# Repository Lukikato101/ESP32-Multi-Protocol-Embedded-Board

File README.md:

# Multi-Protocol ESP32-Based Embedded Board

## Project Overview
This project is my personal embedded hardware design built around the ESP32 platform. I created this board as a compact and flexible prototype for wireless and connected applications. The design is made in KiCad and focuses on a clean PCB structure, practical connectivity, and room for future development.

I made this project to improve my understanding of embedded systems, PCB design, and hardware prototyping. It also helped me practice turning an idea into a more structured and realistic electronic board.

---

## What I Built
This board is centered around an ESP32-based module and several connector interfaces that allow me to connect external components or modules when needed. The layout is simple, organized, and intended to be useful for experimentation and further development.

### Main Parts of the Project
- ESP32-based controller module
- Connector headers for expansion and external connections
- PCB layout designed for practical routing and assembly
- A compact hardware platform for embedded projects

---

## Why I Made This Project
I wanted to build a small hardware platform that could be used as a base for future electronics projects. This board gives me a starting point for testing ideas, connecting modules, and exploring how embedded systems can be designed in a more complete way.

This project is especially useful for:
- learning embedded hardware design
- building wireless-based prototypes
- testing ideas before making a larger product
- improving my PCB and circuit layout skills

---

## Project Images

### PCB Layout

### Board View 1

### Board View 2

---

## What I Learned
Through this project, I improved my understanding of:
- embedded system architecture
- PCB schematic and layout design
- component placement and routing
- hardware organization for practical use
- building a project from concept to board design

---

## Future Development
I can continue developing this project by:
- adding power management features
- integrating sensors or actuators
- supporting more communication interfaces
- turning it into a more complete prototype
- testing it in real applications

---

## Conclusion
This project is an important part of my learning in electronics and embedded hardware. I built it as a personal prototype to strengthen my skills and create a solid foundation for future projects.

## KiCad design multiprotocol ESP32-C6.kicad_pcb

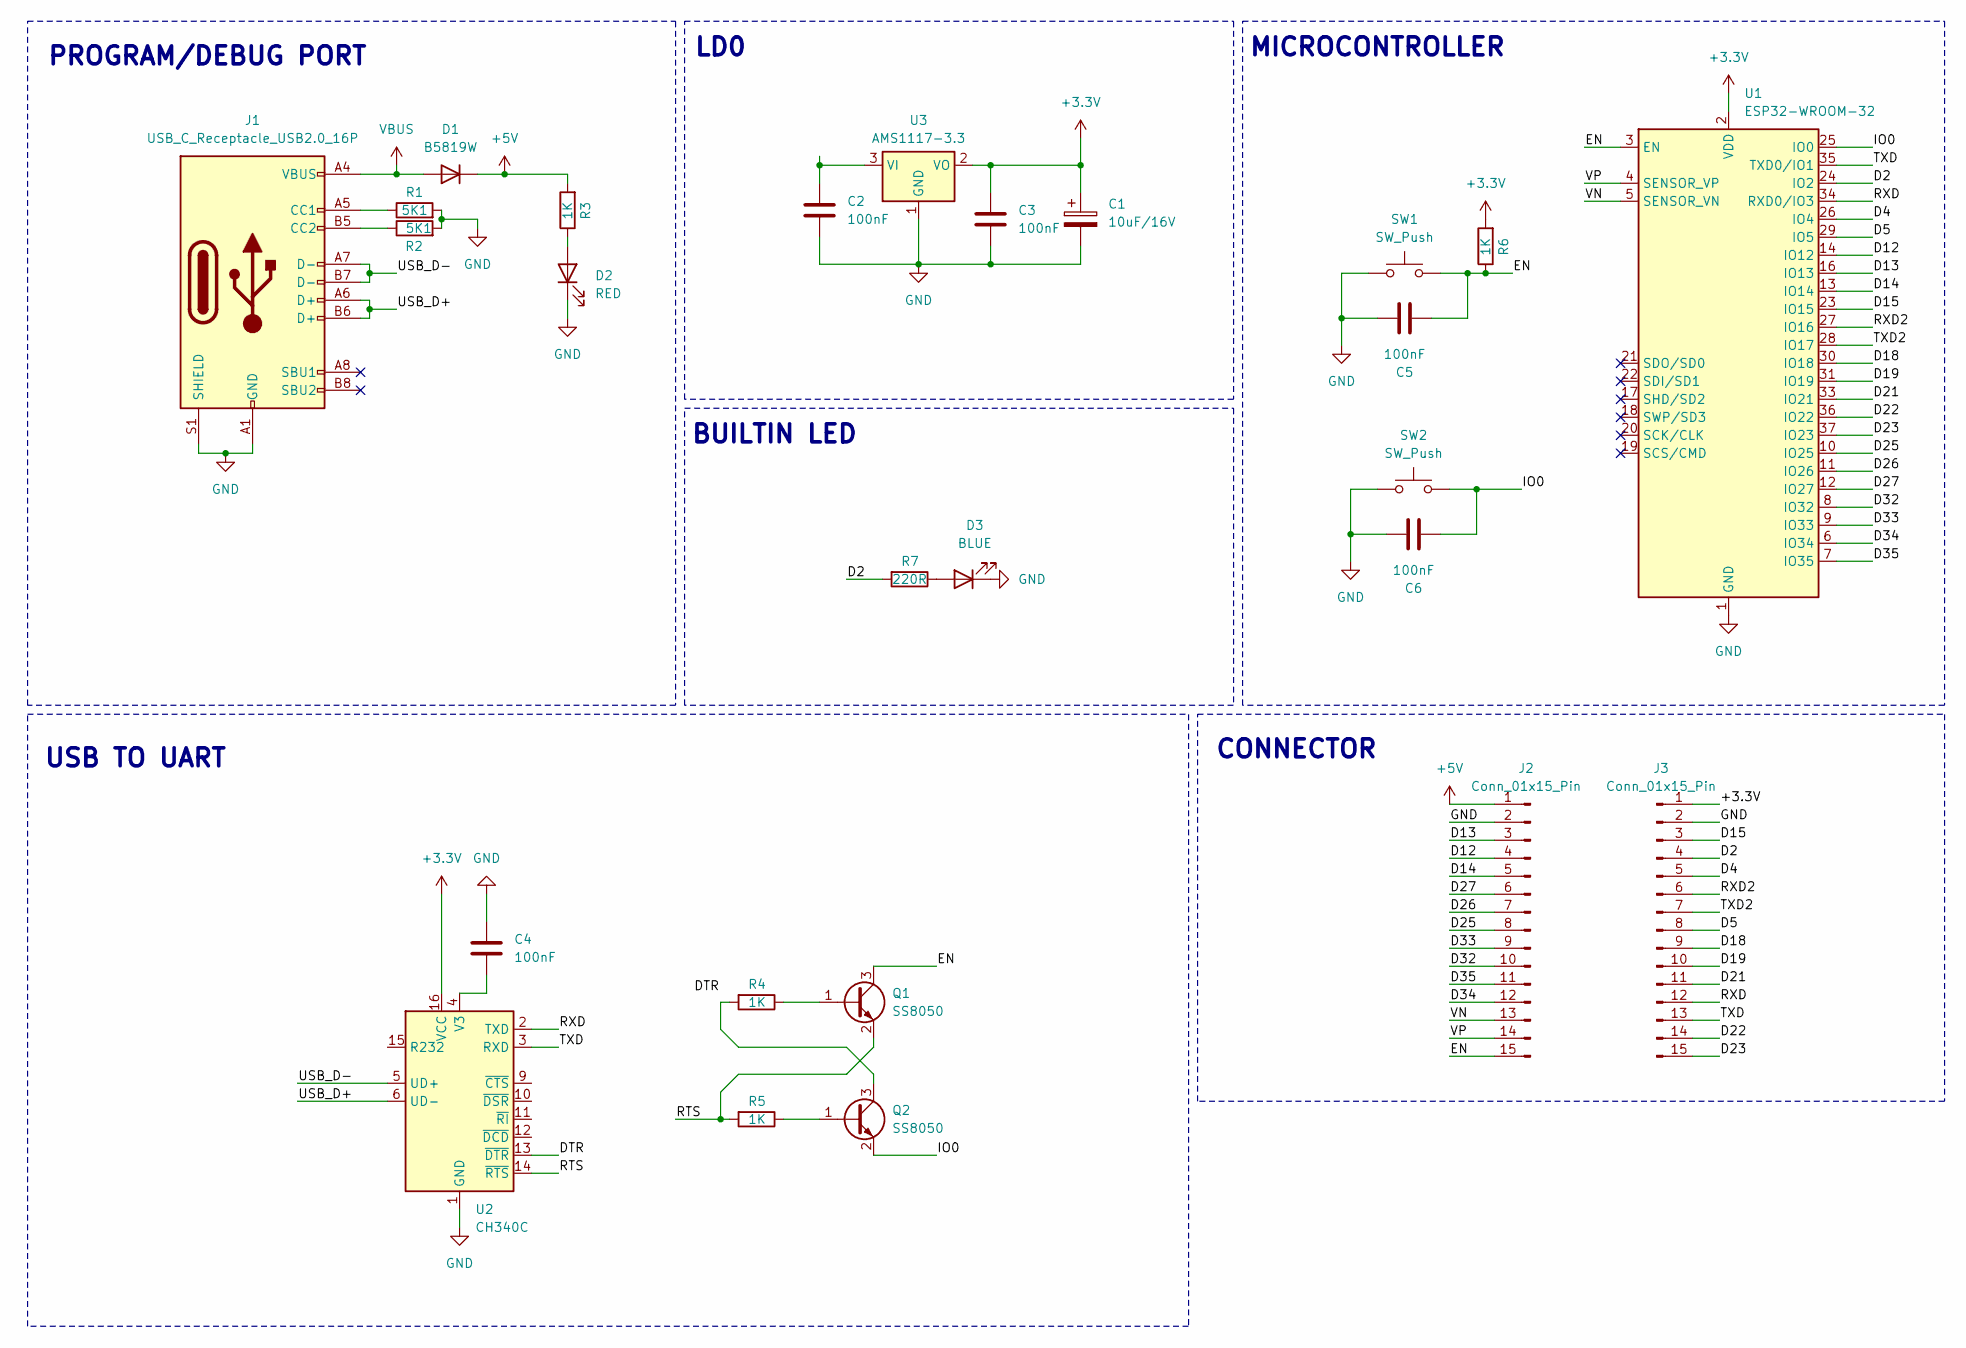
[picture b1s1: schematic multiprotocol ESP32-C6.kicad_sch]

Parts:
C1: 10uF/16V; CP_EIA-3216-10_Kemet-I
C2, C3, C4, C5, C6: 100nF; C_0603_1608Metric
D1: B5819W; D_SOD-123
D2: RED; LED_0603_1608Metric
D3: BLUE; LED_0603_1608Metric
J1: USB_C_Receptacle_USB2.0_16P; USB_C_Receptacle_HRO_TYPE-C-31-M-12
J2, J3: Conn_01x15_Pin; PinHeader_1x15_P2.54mm_Vertical
Q1, Q2: SS8050; SOT-23
R1, R2: 5K1; R_0603_1608Metric
R3, R4, R5, R6: 1K; R_0603_1608Metric
R7: 220R; R_0603_1608Metric
SW1, SW2: SW_Push; SW_Push_SPST_NO_Alps_SKRK
U1: ESP32-WROOM-32
U2: CH340C; SOIC-16_3.9x9.9mm_P1.27mm
U3: AMS1117-3.3; SOT-223-3_TabPin2

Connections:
+3.3V: C1.1, C3.1, J3.1, R6.2, U1.2 (VDD), U2.16 (VCC), U3.2 (VO)
+5V: D1.1 (K), J2.1, R3.2
/D2: J3.4, R7.2, U1.24 (IO2)
/D4: J3.5, U1.26 (IO4)
/D5: J3.8, U1.29 (IO5)
/D12: J2.4, U1.14 (IO12)
/D13: J2.3, U1.16 (IO13)
/D14: J2.5, U1.13 (IO14)
/D15: J3.3, U1.23 (IO15)
/D18: J3.9, U1.30 (IO18)
/D19: J3.10, U1.31 (IO19)
/D21: J3.11, U1.33 (IO21)
/D22: J3.14, U1.36 (IO22)
/D23: J3.15, U1.37 (IO23)
/D25: J2.8, U1.10 (IO25)
/D26: J2.7, U1.11 (IO26)
/D27: J2.6, U1.12 (IO27)
/D32: J2.10, U1.8 (IO32)
/D33: J2.9, U1.9 (IO33)
/D34: J2.12, U1.6 (IO34)
/D35: J2.11, U1.7 (IO35)
/DTR: U2.13 (~DTR)
/EN: C5.1, J2.15, Q1.3 (C), R6.1, SW1.2, U1.3 (EN)
/IO0: C6.1, Q2.2 (E), SW2.2, U1.25 (IO0)
/RTS: Q1.2 (E), R5.2, U2.14 (~RTS)
/RXD: J3.12, U1.34 (RXD0/IO3), U2.2 (TXD)
/RXD2: J3.6, U1.27 (IO16)
/TXD: J3.13, U1.35 (TXD0/IO1), U2.3 (RXD)
/TXD2: J3.7, U1.28 (IO17)
/USB_D+: J1.A6 (D+), J1.B6 (D+), U2.6 (UD-)
/USB_D-: J1.A7 (D-), J1.B7 (D-), U2.5 (UD+)
/VN: J2.13, U1.5 (SENSOR_VN)
/VP: J2.14, U1.4 (SENSOR_VP)
GND: C1.2, C2.2, C3.2, C4.1, C5.2, C6.2, D2.1 (K), D3.1 (K), J1.A1 (GND), J1.A12 (GND), J1.B1 (GND), J1.B12 (GND), J1.S1 (SHIELD), J2.2, J3.2, R1.2, R2.2, SW1.1, SW2.1, U1.1 (GND), U1.15 (GND), U1.38 (GND), U1.39 (GND), U2.1 (GND), U3.1 (GND)
unnamed: D2.2 (A), R3.1
unnamed: D3.2 (A), R7.1
unnamed: J1.A5 (CC1), R1.1
unnamed: J1.B5 (CC2), R2.1
unnamed: Q1.1 (B), R4.1
unnamed: Q2.1 (B), R5.1
unnamed: Q2.3 (C), R4.2
unnamed: C4.2, U2.4 (V3)
unnamed: C2.1, U3.3 (VI)
VBUS: D1.2 (A), J1.A4 (VBUS), J1.A9 (VBUS), J1.B4 (VBUS), J1.B9 (VBUS)

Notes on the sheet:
USB TO UART
BUILTIN LED
PROGRAM/DEBUG PORT
MICROCONTROLLER
LD0
CONNECTOR

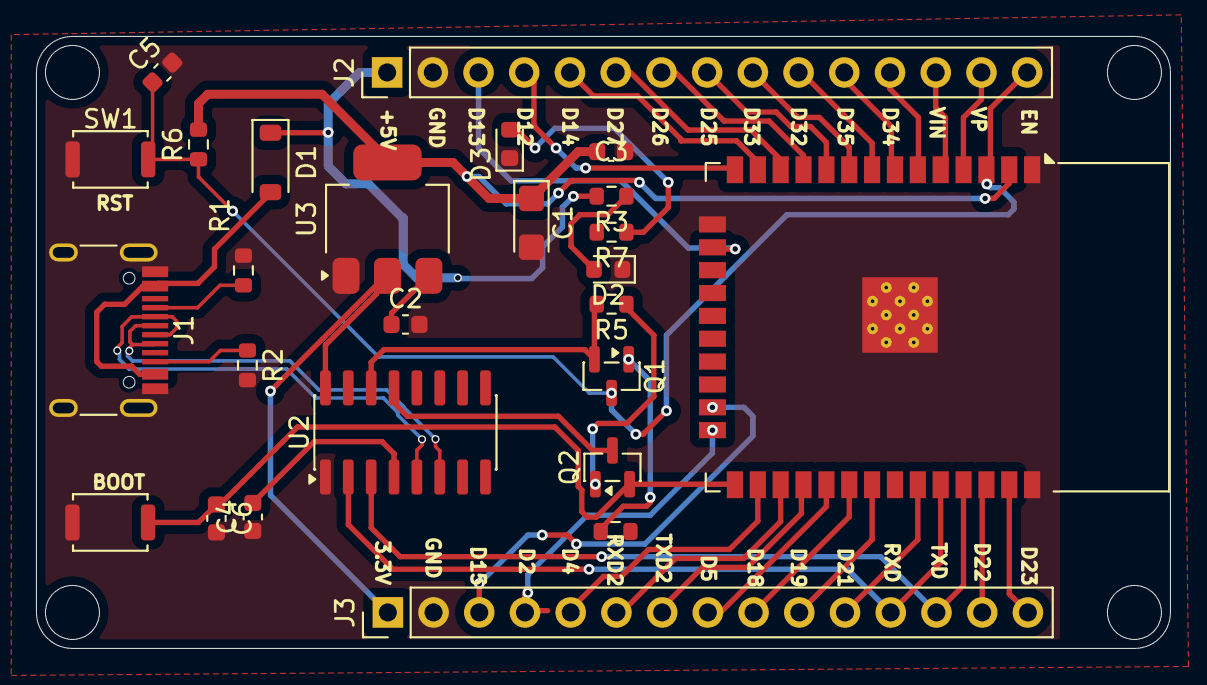
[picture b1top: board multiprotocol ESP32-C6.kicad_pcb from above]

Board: 2 copper layers, 63.0 x 34.0 mm, 26 parts (0 on the bottom side), 43 nets.
